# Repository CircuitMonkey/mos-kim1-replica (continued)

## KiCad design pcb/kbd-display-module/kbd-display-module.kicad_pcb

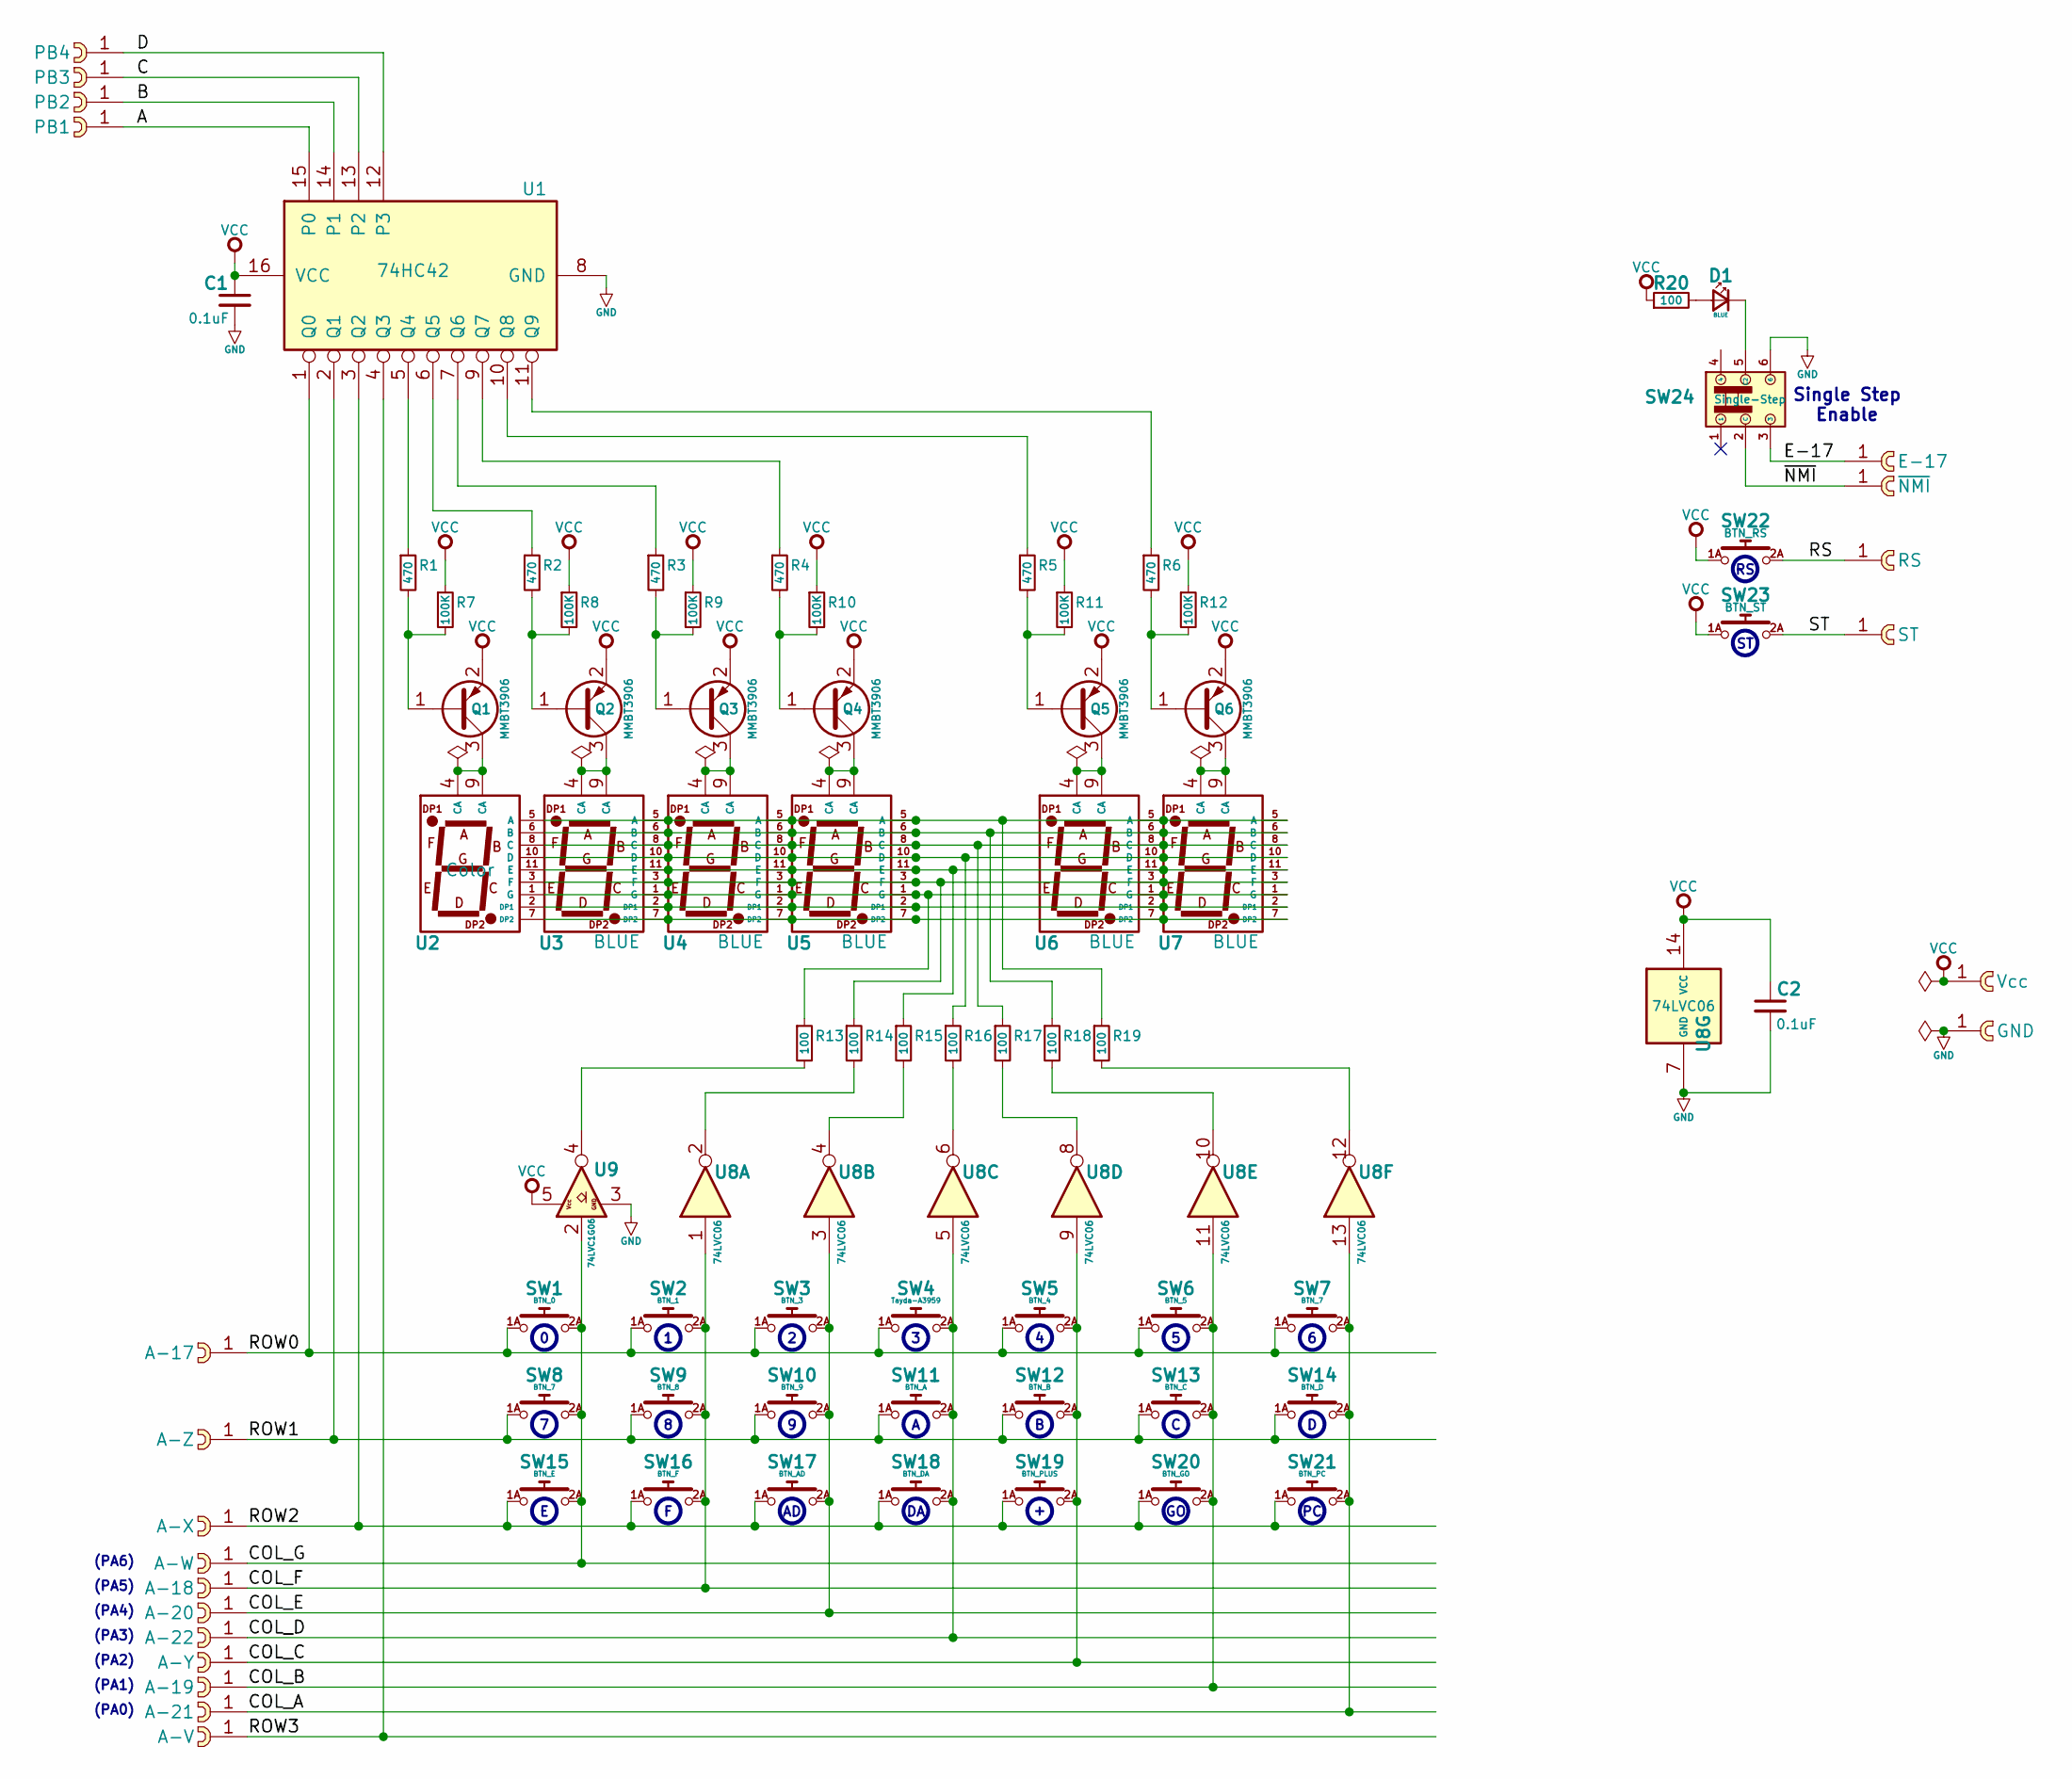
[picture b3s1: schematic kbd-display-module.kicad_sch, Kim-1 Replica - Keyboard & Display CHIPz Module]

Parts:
C1, C2: 0.1uF; C_0603_1608Metric
CST1: PB4; cast-2.0-01P
CST2: PB3; cast-2.0-01P
CST3: PB2; cast-2.0-01P
CST4: PB1; cast-2.0-01P
CST5: E-17; cast-2.0-01P
CST6: ~{NMI}; cast-2.0-01P
CST7: RS; cast-2.0-01P
CST8: ST; cast-2.0-01P
CST9: Vcc; cast-2.0-01P
CST10: GND; cast-2.0-01P
CST11: A-17; cast-2.0-01P
CST12: A-Z; cast-2.0-01P
CST13: A-X; cast-2.0-01P
CST14: A-W; cast-2.0-01P
CST15: A-18; cast-2.0-01P
CST16: A-20; cast-2.0-01P
CST17: A-22; cast-2.0-01P
CST18: A-Y; cast-2.0-01P
CST19: A-19; cast-2.0-01P
CST20: A-21; cast-2.0-01P
CST21: A-V; cast-2.0-01P
D1: BLUE; LED_0603_1608Metric
Q1, Q2, Q3, Q4, Q5, Q6: MMBT3906; SOT-23
R1, R2, R3, R4, R5, R6: 470; R_0603_1608Metric
R7, R8, R9, R10, R11, R12: 100K; R_0603_1608Metric
R13, R14, R15, R16, R17, R18, R19, R20: 100; R_0603_1608Metric
SW1: BTN_0; Tactile_CK_KSC_6x6_Gullwing
SW2: BTN_1; Tactile_CK_KSC_6x6_Gullwing
SW3: BTN_3; Tactile_CK_KSC_6x6_Gullwing
SW4: Tayda-A3959; Tactile_CK_KSC_6x6_Gullwing
SW5: BTN_4; Tactile_CK_KSC_6x6_Gullwing
SW6: BTN_5; Tactile_CK_KSC_6x6_Gullwing
SW7, SW8: BTN_7; Tactile_CK_KSC_6x6_Gullwing
SW9: BTN_8; Tactile_CK_KSC_6x6_Gullwing
SW10: BTN_9; Tactile_CK_KSC_6x6_Gullwing
SW11: BTN_A; Tactile_CK_KSC_6x6_Gullwing
SW12: BTN_B; Tactile_CK_KSC_6x6_Gullwing
SW13: BTN_C; Tactile_CK_KSC_6x6_Gullwing
SW14: BTN_D; Tactile_CK_KSC_6x6_Gullwing
SW15: BTN_E; Tactile_CK_KSC_6x6_Gullwing
SW16: BTN_F; Tactile_CK_KSC_6x6_Gullwing
SW17: BTN_AD; Tactile_CK_KSC_6x6_Gullwing
SW18: BTN_DA; Tactile_CK_KSC_6x6_Gullwing
SW19: BTN_PLUS; Tactile_CK_KSC_6x6_Gullwing
SW20: BTN_GO; Tactile_CK_KSC_6x6_Gullwing
SW21: BTN_PC; Tactile_CK_KSC_6x6_Gullwing
SW22: BTN_RS; Tactile_CK_KSC_6x6_Gullwing
SW23: BTN_ST; Tactile_CK_KSC_6x6_Gullwing
SW24: Single-Step; CK_JS202011SC_SLIDE_DPDT_SMT_9x3.6; MPN CK JS202011SC
U1: 74HC42; SO-16_3.9x9.9mm_P1.27mm
U2: Color; Avago-HDSM-281x-283x-SevenSeg; MPN Avago HDSM-281B
U3, U4, U5, U6, U7: BLUE; Avago-HDSM-281x-283x-SevenSeg; MPN Avago HDSM-281B
U8: 74LVC06; SOIC-14_3.9x8.7mm_P1.27mm
U9: 74LVC1G06; SOT-553

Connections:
/COL_A: CST20.1, SW7.2A, SW7.2B, SW14.2A, SW14.2B, SW21.2A, SW21.2B, U8.13
/COL_B: CST19.1, SW6.2A, SW6.2B, SW13.2A, SW13.2B, SW20.2A, SW20.2B, U8.11
/COL_C: CST18.1, SW5.2A, SW5.2B, SW12.2A, SW12.2B, SW19.2A, SW19.2B, U8.9
/COL_D: CST17.1, SW4.2A, SW4.2B, SW11.2A, SW11.2B, SW18.2A, SW18.2B, U8.5
/COL_E: CST16.1, SW3.2A, SW3.2B, SW10.2A, SW10.2B, SW17.2A, SW17.2B, U8.3
/COL_F: CST15.1, SW2.2A, SW2.2B, SW9.2A, SW9.2B, SW16.2A, SW16.2B, U8.1
/COL_G: CST14.1, SW1.2A, SW1.2B, SW8.2A, SW8.2B, SW15.2A, SW15.2B, U9.2
/E-17: CST5.1, SW24.3
/ROW0: CST11.1, SW1.1A, SW1.1B, SW2.1A, SW2.1B, SW3.1A, SW3.1B, SW4.1A, SW4.1B, SW5.1A, SW5.1B, SW6.1A, SW6.1B, SW7.1A, SW7.1B, U1.1 (Q0)
/ROW1: CST12.1, SW8.1A, SW8.1B, SW9.1A, SW9.1B, SW10.1A, SW10.1B, SW11.1A, SW11.1B, SW12.1A, SW12.1B, SW13.1A, SW13.1B, SW14.1A, SW14.1B, U1.2 (Q1)
/ROW2: CST13.1, SW15.1A, SW15.1B, SW16.1A, SW16.1B, SW17.1A, SW17.1B, SW18.1A, SW18.1B, SW19.1A, SW19.1B, SW20.1A, SW20.1B, SW21.1A, SW21.1B, U1.3 (Q2)
/ROW3: CST21.1, U1.4 (Q3)
/RS: CST7.1, SW22.2A, SW22.2B
/ST: CST8.1, SW23.2A, SW23.2B
/~NMI: CST6.1, SW24.2 (C)
GND: C1.2, C2.2, CST10.1, SW24.6, U1.8 (GND), U8.7 (GND), U9.3
unnamed: D1.2 (A), R20.2
unnamed: D1.1 (K), SW24.5 (C2)
unnamed: Q1.1 (B), R1.2, R7.2
unnamed: Q1.3 (C), U2.4 (CA), U2.9 (CA)
unnamed: Q2.1 (B), R2.2, R8.2
unnamed: Q2.3 (C), U3.4 (CA), U3.9 (CA)
unnamed: Q3.1 (B), R3.2, R9.2
unnamed: Q3.3 (C), U4.4 (CA), U4.9 (CA)
unnamed: Q4.1 (B), R4.2, R10.2
unnamed: Q4.3 (C), U5.4 (CA), U5.9 (CA)
unnamed: Q5.1 (B), R5.2, R11.2
unnamed: Q5.3 (C), U6.4 (CA), U6.9 (CA)
unnamed: Q6.1 (B), R6.2, R12.2
unnamed: Q6.3 (C), U7.4 (CA), U7.9 (CA)
unnamed: R13.2, U9.4
unnamed: R14.2, U8.2
unnamed: R15.2, U8.4
unnamed: R16.2, U8.6
unnamed: R17.2, U8.8
unnamed: R18.2, U8.10
unnamed: R19.2, U8.12
unnamed: CST4.1, U1.15 (P0)
unnamed: CST3.1, U1.14 (P1)
unnamed: CST2.1, U1.13 (P2)
unnamed: CST1.1, U1.12 (P3)
unnamed: R1.1, U1.5 (Q4)
unnamed: R2.1, U1.6 (Q5)
unnamed: R3.1, U1.7 (Q6)
unnamed: R4.1, U1.9 (Q7)
unnamed: R5.1, U1.10 (Q8)
unnamed: R6.1, U1.11 (Q9)
unnamed: R19.1, U2.5 (A), U3.5 (A), U4.5 (A), U5.5 (A), U6.5 (A), U7.5 (A)
unnamed: R18.1, U2.6 (B), U3.6 (B), U4.6 (B), U5.6 (B), U6.6 (B), U7.6 (B)
unnamed: R17.1, U2.8 (C), U3.8 (C), U4.8 (C), U5.8 (C), U6.8 (C), U7.8 (C)
unnamed: R16.1, U2.10 (D), U3.10 (D), U4.10 (D), U5.10 (D), U6.10 (D), U7.10 (D)
unnamed: U2.2 (DP1), U3.2 (DP1), U4.2 (DP1), U5.2 (DP1), U6.2 (DP1), U7.2 (DP1)
unnamed: U2.7 (DP2), U3.7 (DP2), U4.7 (DP2), U5.7 (DP2), U6.7 (DP2), U7.7 (DP2)
unnamed: R15.1, U2.11 (E), U3.11 (E), U4.11 (E), U5.11 (E), U6.11 (E), U7.11 (E)
unnamed: R14.1, U2.3 (F), U3.3 (F), U4.3 (F), U5.3 (F), U6.3 (F), U7.3 (F)
unnamed: R13.1, U2.1 (G), U3.1 (G), U4.1 (G), U5.1 (G), U6.1 (G), U7.1 (G)
VCC: C1.1, C2.1, CST9.1, Q1.2 (E), Q2.2 (E), Q3.2 (E), Q4.2 (E), Q5.2 (E), Q6.2 (E), R7.1, R8.1, R9.1, R10.1, R11.1, R12.1, R20.1, SW22.1A, SW22.1B, SW23.1A, SW23.1B, U1.16 (VCC), U8.14 (VCC), U9.5

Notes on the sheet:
Single Step Enable
(PA1)
(PA0)
(PA6)
(PA3)
(PA2)
(PA4)
(PA5)

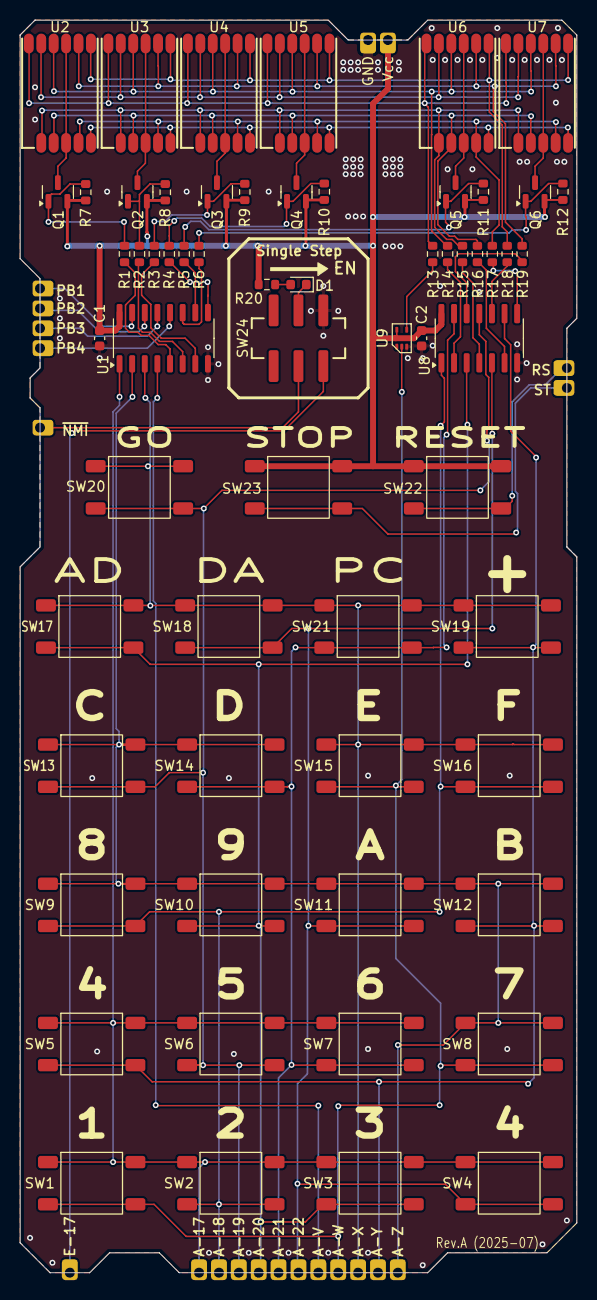
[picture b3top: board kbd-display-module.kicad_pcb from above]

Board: 2 copper layers, 56.0 x 126.0 mm, 83 parts (0 on the bottom side), 57 nets.

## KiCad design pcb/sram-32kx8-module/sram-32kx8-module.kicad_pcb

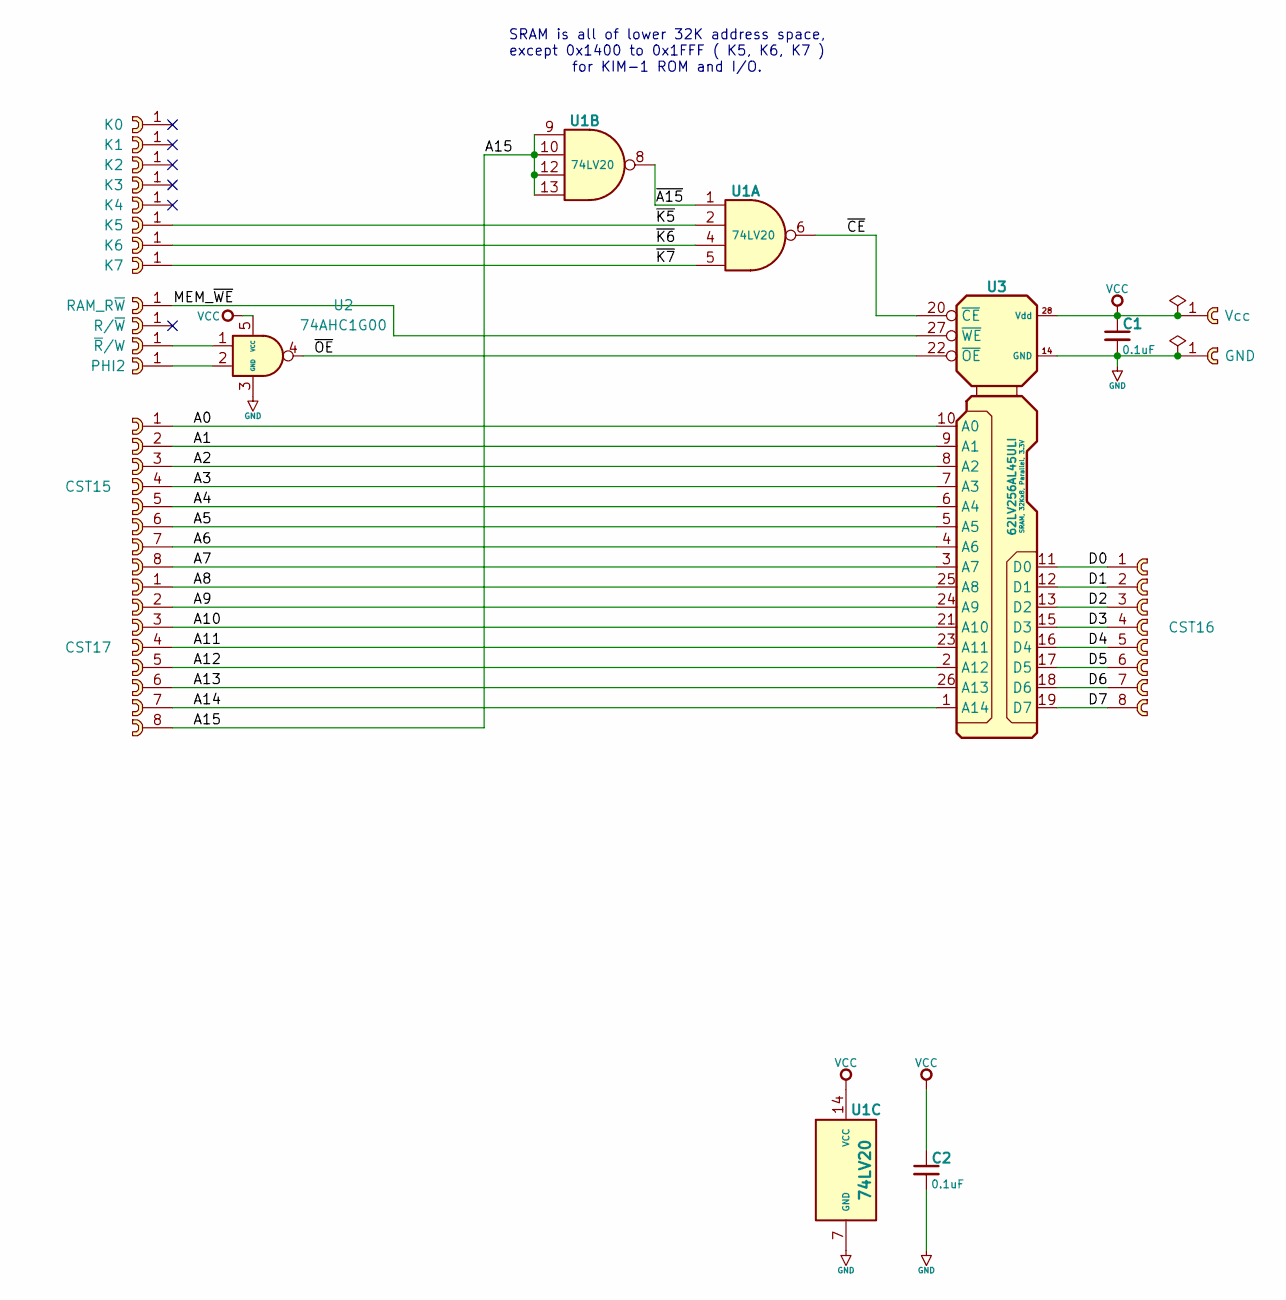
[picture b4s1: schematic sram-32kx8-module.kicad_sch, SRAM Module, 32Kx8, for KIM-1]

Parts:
C1, C2: 0.1uF; C_0603_1608Metric
CST1: K0; cast-2.0-01P
CST2: K1; cast-2.0-01P
CST3: K2; cast-2.0-01P
CST4: K3; cast-2.0-01P
CST5: K4; cast-2.0-01P
CST6: K5; cast-2.0-01P
CST7: K6; cast-2.0-01P
CST8: K7; cast-2.0-01P
CST9: RAM_R~{W}; cast-2.0-01P
CST10: Vcc; cast-2.0-01P
CST11: R/~{W}; cast-2.0-01P
CST12: ~{R}/W; cast-2.0-01P
CST13: GND; cast-2.0-01P
CST14: PHI2; cast-2.0-01P
CST15, CST16, CST17: DATA I/O; cast-2.0-08P
U1: 74LV20; SOIC-14_3.9x8.7mm_P1.27mm
U2: 74AHC1G00; SOT-353_SC-70-5; MPN MC74HC1G00DFT1G
U3: 62LV256AL45ULI; SOIC-28_18x9

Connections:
/A0: CST15.1, U3.10 (A0)
/A1: CST15.2, U3.9 (A1)
/A2: CST15.3, U3.8 (A2)
/A3: CST15.4, U3.7 (A3)
/A4: CST15.5, U3.6 (A4)
/A5: CST15.6, U3.5 (A5)
/A6: CST15.7, U3.4 (A6)
/A7: CST15.8, U3.3 (A7)
/A8: CST17.1, U3.25 (A8)
/A9: CST17.2, U3.24 (A9)
/A10: CST17.3, U3.21 (A10)
/A11: CST17.4, U3.23 (A11)
/A12: CST17.5, U3.2 (A12)
/A13: CST17.6, U3.26 (A13)
/A14: CST17.7, U3.1 (A14)
/A15: CST17.8, U1.9, U1.10, U1.12, U1.13
/D0: CST16.1, U3.11 (D0)
/D1: CST16.2, U3.12 (D1)
/D2: CST16.3, U3.13 (D2)
/D3: CST16.4, U3.15 (D3)
/D4: CST16.5, U3.16 (D4)
/D5: CST16.6, U3.17 (D5)
/D6: CST16.7, U3.18 (D6)
/D7: CST16.8, U3.19 (D7)
/MEM_~WE: CST9.1, U3.27 (~WE)
/~A15: U1.1, U1.8
/~CE: U1.6, U3.20 (~CE)
/~K5: CST6.1, U1.2
/~K6: CST7.1, U1.4
/~K7: CST8.1, U1.5
/~OE: U2.4, U3.22 (~OE)
GND: C1.2, C2.2, CST13.1, U1.7 (GND), U2.3 (GND), U3.14 (GND)
unnamed: CST12.1, U2.1
unnamed: CST14.1, U2.2
VCC: C1.1, C2.1, CST10.1, U1.14 (VCC), U2.5 (VCC), U3.28 (Vdd)

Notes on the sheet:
SRAM is all of lower 32K address space, except 0x1400 to 0x1FFF ( K5, K6, K7 ) for KIM-1 ROM and I/O.

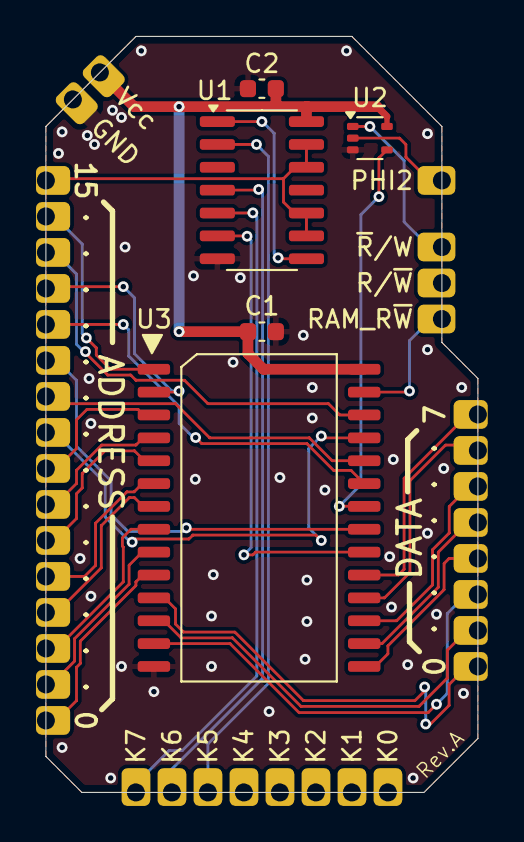
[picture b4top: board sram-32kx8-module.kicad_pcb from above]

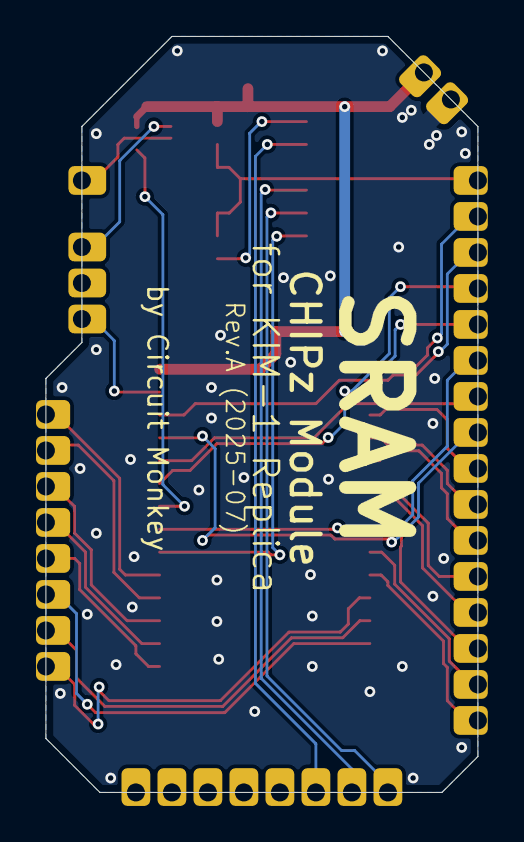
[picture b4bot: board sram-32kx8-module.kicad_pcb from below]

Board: 2 copper layers, 24.0 x 42.0 mm, 22 parts (2 on the bottom side), 35 nets.

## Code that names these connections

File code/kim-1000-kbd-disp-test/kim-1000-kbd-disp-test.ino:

/*
  Keyboard and Display Module tester for KIM-1000

  This code will test/exercise the individual board module used the
  KIM-1000 using a RPi2040 Pico.

  Pico was chosen as it works at 3V IO levels. Most ATmega are 5V.

  by Circuit Monkey - 2025

  License: MIT
  This code is in the public domain. Free to study/copy/change.
*/
#define LED LED_BUILTIN  // the pin the LED is attached to

#define DEC_A 2
#define DEC_B 3
#define DEC_C 4
#define DEC_D 5

#define COL_A 6   // LED Top
#define COL_B 7   // LED Upper-Right
#define COL_C 8   // LED Lower-Right
#define COL_D 9   // LED Bottom
#define COL_E 10  // LED Lower-Left
#define COL_F 11  // LED Upper-Left
#define COL_G 12  // LED Center segment

int cols[7] = { COL_A, COL_B, COL_C, COL_D, COL_E, COL_F, COL_G };

#define CHAR_TABLE 17  // number of elements in segs table.
int segs[CHAR_TABLE][7] = {
  // t,ru,rl,b,ll,lu,c
  { 1, 1, 1, 1, 1, 1, 0 },  // 0
  { 0, 1, 1, 0, 0, 0, 0 },  // 1
  { 1, 1, 0, 1, 1, 0, 1 },  // 2
  { 1, 1, 1, 1, 0, 0, 1 },  // 3
  { 0, 1, 1, 0, 0, 1, 1 },  // 4
  { 1, 0, 1, 1, 0, 1, 1 },  // 5
  { 1, 0, 1, 1, 1, 1, 1 },  // 6
  { 1, 1, 1, 0, 0, 0, 0 },  // 7
  { 1, 1, 1, 1, 1, 1, 1 },  // 8
  { 1, 1, 1, 1, 0, 1, 1 },  // 9
  { 1, 1, 1, 0, 1, 1, 1 },  // A
  { 0, 0, 1, 1, 1, 1, 1 },  // b
  { 1, 0, 0, 1, 1, 1, 0 },  // C
  { 0, 1, 1, 1, 1, 0, 1 },  // d
  { 1, 0, 0, 1, 1, 1, 1 },  // E
  { 1, 0, 0, 0, 1, 1, 1 },  // F
  { 0, 0, 0, 0, 0, 0, 1 }   // -

};

//       A    B    C    D    E    F    G
// --------------------------------------
//  0 |   6    5    4    3    2    1    0
//  1 |   D    C    B    A    9    8    7
//  2 |   PC   GO   +    DA   AD   F    E
//  3 |   x    x    x    x    x    x    x
char keys[3][7] = {
  { '6', '5', '4', '3', '2', '1', '0' },
  { 'D', 'C', 'B', 'A', '9', '8', '7' },
  { 'P', 'G', '+', 'X', 'Y', 'F', 'E' }  // P=PG, G=Go, X=DA, Y=AD

};

char lastKey = '*';  // Undefined.

// the setup routine runs once when you press reset:
void setup() {
  pinMode(LED, OUTPUT);
  Serial.begin(9600);
  while (!Serial) {
    digitalWrite(LED, HIGH);  // turn the LED on (HIGH is the voltage level)
    delay(1000);              // wait for a second
    digitalWrite(LED, LOW);   // turn the LED off by making the voltage LOW
    delay(1000);
  }
  analogWrite(LED, 200);

  pinMode(DEC_A, OUTPUT);
  pinMode(DEC_B, OUTPUT);
  pinMode(DEC_C, OUTPUT);
  pinMode(DEC_D, OUTPUT);

  testDisplay();
}

// the loop routine runs over and over again forever:
void loop() {
  keyboardTest();
  //analogWrite(LED, 0);

  //delay(300);
  //analogWrite(LED, 200);
}

void testDisplay() {
  // Output Mode COL_x lines
  pinMode(COL_A, OUTPUT);
  pinMode(COL_B, OUTPUT);
  pinMode(COL_C, OUTPUT);
  pinMode(COL_D, OUTPUT);
  pinMode(COL_E, OUTPUT);
  pinMode(COL_F, OUTPUT);
  pinMode(COL_G, OUTPUT);

  // Set the decoder line/column to perform work on.
  // Perform test on each segment array.
  for (int i = 4; i < 10; i++) {
    digitalWrite(DEC_A, i & 0x1);
    digitalWrite(DEC_B, (i >> 1) & 0x1);
    digitalWrite(DEC_C, (i >> 2) & 0x1);
    digitalWrite(DEC_D, (i >> 3) & 0x1);

    // Exercise display segments.
    for (int j = 0; j < CHAR_TABLE; j++) {
      seg(j);  // Show char i from segs table.
      delay(200);
    }
  }
}

// LED Segments Test
// Assert COL_x for each segment
void keyboardTest() {
  // Output Mode COL_x lines
  // Input Pullup Mode COL_x lines.
  pinMode(COL_A, INPUT_PULLUP);
  pinMode(COL_B, INPUT_PULLUP);
  pinMode(COL_C, INPUT_PULLUP);
  pinMode(COL_D, INPUT_PULLUP);
  pinMode(COL_E, INPUT_PULLUP);
  pinMode(COL_F, INPUT_PULLUP);
  pinMode(COL_G, INPUT_PULLUP);

  // Set the decoder line/column to perform work on.
  // Perform test on each segment array.
  for (int i = 0; i < 4; i++) {
    digitalWrite(DEC_A, i & 0x1);
    digitalWrite(DEC_B, (i >> 1) & 0x1);
    digitalWrite(DEC_C, (i >> 2) & 0x1);
    digitalWrite(DEC_D, (i >> 3) & 0x1);

    if (i == 3) continue;  // No presses on row 3.

    int press = scanCols(i);
    if (press < 7) {
      char key = keys[i][press];
      if (lastKey == key) {continue;}
      Serial.print("Key pressed: ");
      Serial.println(key);
      lastKey = key;
    }
  }
}


// Keyboard Test
// Read each COL_x. 0==pressed.
int scanCols(int row) {
  for (int i = 0; i < 7; i++) {
    if (!digitalRead(cols[i])) {  // Not pressed = 1.
      return i;
    }
  }

  return 7;
}

void seg(int i) {
  digitalWrite(COL_A, segs[i][0]);
  digitalWrite(COL_B, segs[i][1]);
  digitalWrite(COL_C, segs[i][2]);
  digitalWrite(COL_D, segs[i][3]);
  digitalWrite(COL_E, segs[i][4]);
  digitalWrite(COL_F, segs[i][5]);
  digitalWrite(COL_G, segs[i][6]);
}

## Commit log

2025-07-20 RevA Sent to Fab.
2025-07-23 Created Rev.A for Keyboard-Display Module
2025-07-25 Created SRAM module, Rev.A
2025-07-27 Fix ERC Errors
2025-07-27 Add 3D model.
2025-07-27 3D model for SRAM CHIPz Module
2025-08-05 Develop logo artwork.
2025-08-05 Tune Keyboard module design.
2025-08-05 Rev-A of KIM-1 Replica. Final???
2025-08-05 Create fp-lib-table
2025-08-05 Create sym-lib-table
2025-08-05 Add 3Dmodel for 22x2 connector.
2025-08-05 Add 3D for USB and expansion connectors.
2025-08-19 Minore changes.
2025-08-19 Add MPN for component.
2025-08-19 Add Note regarding component cost.
2025-08-19 Add BOMs
2025-08-31 Added assembly notes for future changes.
2025-08-31 Added code to test keyboard/display module.
2025-09-02 Add design note to schematic.
2025-09-02 Print schematic to PDF.
2025-09-02 Add test program for SRAM.
2025-09-03 Add PDF schematic for control module.
2025-09-03 Make some corrections. Bump Rev to B.
2025-09-07 Add rework note.
2025-09-09 Final tuning.
2025-09-09 Fix paste mask issue with SRAM component.
2025-09-09 Add gerber setting.
2025-09-10 Gerbers for PCB as ordered on 9-SEP-2025
2025-09-10 Move gerber zip file.
2025-09-22 Update and finalize rev-b board.
2025-11-04 Fix chip reference. Was wrong part number provided.
2025-11-04 Add changes for Rev.C. Clock pin connection issue.
